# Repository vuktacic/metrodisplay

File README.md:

# MD
## Description
MD (metrodisplay) is a big LED matrix assembly with game controls to play pong and tetris (in progress). It's built with four outdoor (very bright) P5 64x32 panels, a custom pcb with an esp32, a cnc'd wooden frame, and power distribution from mains AC. The total cost of the project is under $90 USD.

I was originally making a small project with a single LED panel to display subway times for the Vancouver Skytrain (hence the name), but I realized that while that was great for a static bedroom display, something much more exciting and interactive like this would be much more fun to showcase at Opensauce!

## TODO List
- [x] Pong game
- [ ] Tetris game (in progress)
- [ ] Concept art
- [ ] CNC designs
- [ ] CNC toolpathing
- [ ] CNCing
- [ ] Frame building
- [ ] Electronics Setup
- [ ] Final tests
- [ ] Dismantling
- [ ] Present at Opensauce!

## Structure
- [./cad](./cad): STEP & F3D
- [./pcb](./pcb): PCB Files.
- [./mdcore](./mdcore): Firmware
- [./bom.csv](./bom.csv): Bill of Materials
- [./JOURNAL.md](./JOURNAL.md): Journal

View the PCB on KiCanvas:  

## CAD
### Frame

Frame designed to be disassembled to fit in standard carry-on luggage.

### Controllers

Controllers are 22cm wide

## Electronics
### PCB

### Schematic

### Power Distribution

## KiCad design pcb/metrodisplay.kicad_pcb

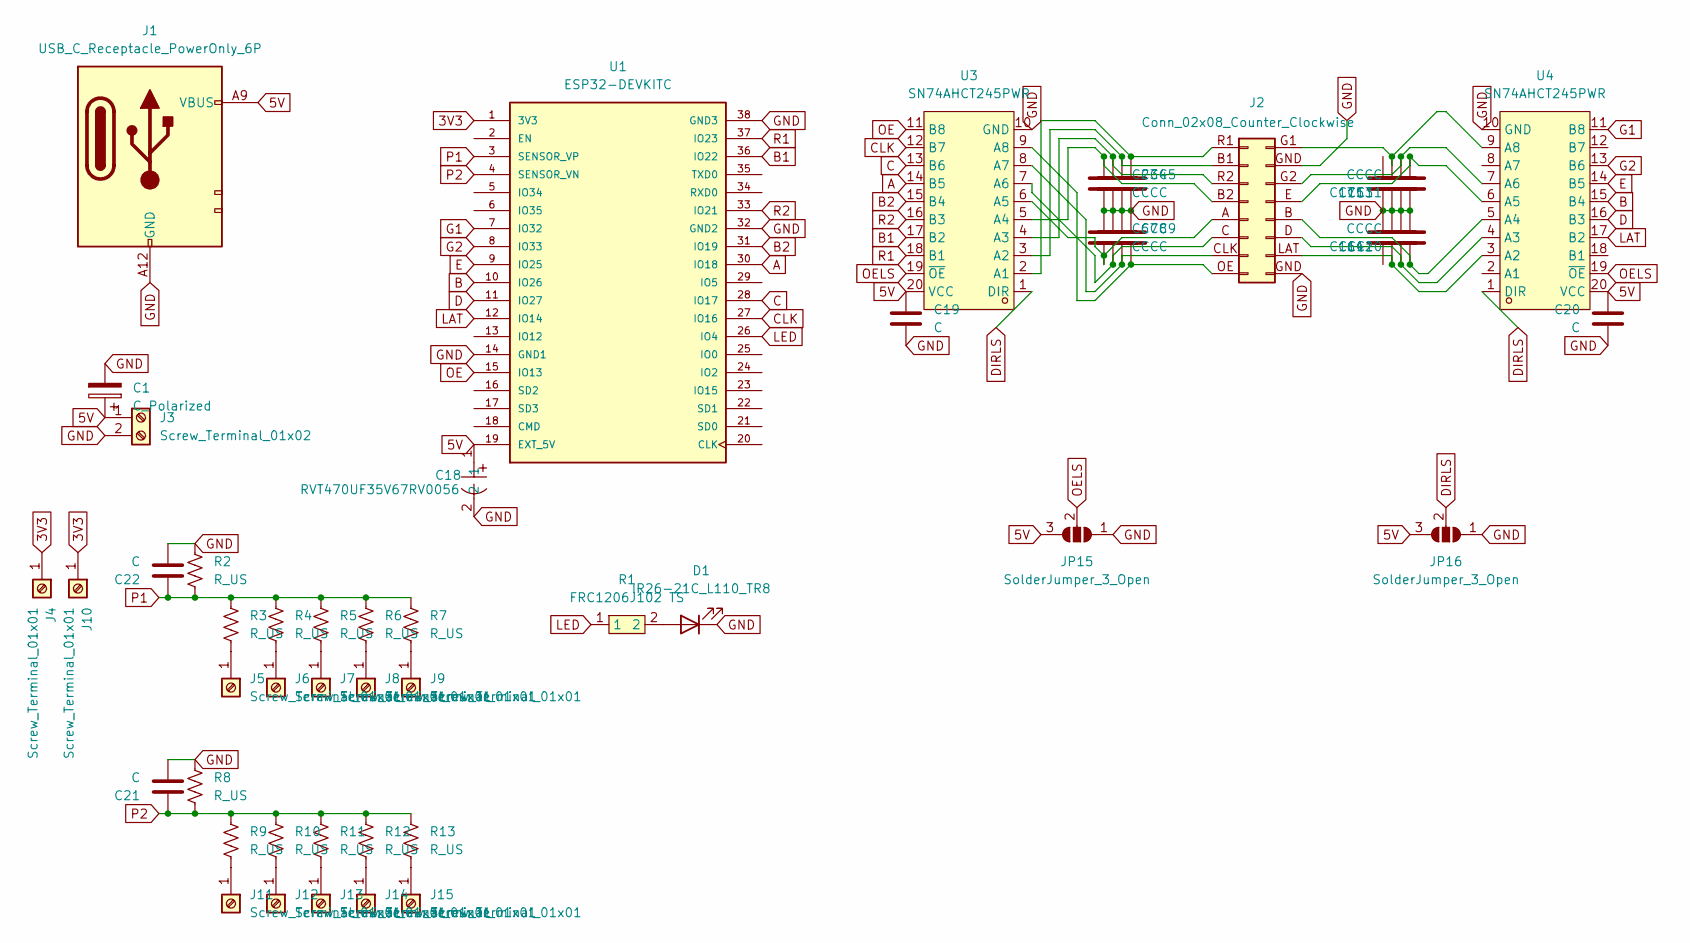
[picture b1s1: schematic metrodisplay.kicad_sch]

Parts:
C1: C_Polarized; CP_Radial_D16.0mm_P7.50mm
C2, C3, C4, C5, C6, C7, C8, C9, C10, C11, C12, C13, C14, C15, C16, C17, C19, C20, C21, C22: C; C1206
C18: RVT470UF35V67RV0056; CAP-SMD_BD10.0-L10.3-W10.3-LS11.0-FD; LCSC Part C2836436
D1: IR26-21C_L110_TR8; LED_1206_3216Metric
J1: USB_C_Receptacle_PowerOnly_6P; USB_C_PD_BOARD
J2: Conn_02x08_Counter_Clockwise; PinHeader_2x08_P2.54mm_Vertical_MD
J3: Screw_Terminal_01x02; TerminalBlock_Dinkle_DT-55-B01X-02_P10.00mm
J4, J5, J6, J7, J8, J9, J10, J11, J12, J13, J14, J15: Screw_Terminal_01x01; SolderWire-0.5sqmm_1x01_D0.9mm_OD2.1mm
JP15, JP16: SolderJumper_3_Open; SolderJumper-3_P2.0mm_Open_TrianglePad1.0x1.5mm
R1: FRC1206J102 TS; R1206; LCSC Part C2907440
R2, R3, R4, R5, R6, R7, R8, R9, R10, R11, R12, R13: R_US; R_Axial_DIN0204_L3.6mm_D1.6mm_P5.08mm_Horizontal
U1: ESP32-DEVKITC; MODULE_ESP32-DEVKITC; PARTREV N/A
U3, U4: SN74AHCT245PWR; TSSOP-20_L6.5-W4.4-P0.65-LS6.4-BL; MPN SN74AHCT245PWR; LCSC Part C10910

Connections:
3V3: J4.1 (Pin_1_1), J10.1 (Pin_1_1), U1.1 (3V3)
5V: C1.1, C18.1, C19.1, C20.1, J1.A9 (VBUS), J3.1, JP15.3 (B), JP16.3 (B), U1.19 (EXT_5V), U3.20 (VCC), U4.20 (VCC)
A: U1.30 (IO18), U3.14 (B5)
B: U1.10 (IO26), U4.15 (B4)
B1: U1.36 (IO22), U3.17 (B2)
B2: U1.31 (IO19), U3.15 (B4)
C: U1.28 (IO17), U3.13 (B6)
CLK: U1.27 (IO16), U3.12 (B7)
D: U1.11 (IO27), U4.16 (B3)
DIRLS: JP16.2 (C), U3.1 (DIR), U4.1 (DIR)
E: U1.9 (IO25), U4.14 (B5)
G1: U1.7 (IO32), U4.11 (B8)
G2: U1.8 (IO33), U4.13 (B6)
GND: C1.2, C2.2, C3.2, C4.2, C5.2, C6.1, C7.1, C8.1, C9.1, C10.2, C11.1, C12.2, C13.1, C14.2, C15.1, C16.2, C17.1, C18.2, C19.2, C20.2, C21.2, C22.2, D1.1 (K), J1.A12 (GND), J2.GND (Pin_9), J3.2, JP15.1 (A), JP16.1 (A), R2.1, R8.1, U1.14 (GND1), U1.32 (GND2), U1.38 (GND3), U3.10 (GND), U4.10 (GND); also elsewhere on the board
LAT: U1.12 (IO14), U4.17 (B2)
LED: R1.1, U1.26 (IO4)
unnamed: D1.2 (A), R1.2
unnamed: C5.1, J2.R1 (Pin_1), U3.2 (A1)
unnamed: C4.1, J2.B1 (Pin_2), U3.3 (A2)
unnamed: C3.1, J2.R2 (Pin_3), U3.4 (A3)
unnamed: C2.1, J2.B2 (Pin_4), U3.5 (A4)
unnamed: C6.2, J2.A (Pin_5), U3.6 (A5)
unnamed: C7.2, J2.C (Pin_6), U3.7 (A6)
unnamed: C8.2, J2.CLK (Pin_7), U3.8 (A7)
unnamed: C9.2, J2.OE (Pin_8), U3.9 (A8)
unnamed: C14.1, J2.LAT (Pin_10), U4.3 (A2)
unnamed: C12.1, J2.D (Pin_11), U4.4 (A3)
unnamed: C10.1, J2.B (Pin_12), U4.5 (A4)
unnamed: C11.2, J2.E (Pin_13), U4.6 (A5)
unnamed: C13.2, J2.G2 (Pin_14), U4.7 (A6)
unnamed: C15.2, J2.G1 (Pin_16), U4.9 (A8)
unnamed 31: J5.1, R3.2; also elsewhere on the board
unnamed: J6.1 (Pin_1_1), R4.2
unnamed: J7.1 (Pin_1_1), R5.2
unnamed: J8.1 (Pin_1_1), R6.2
unnamed: J9.1 (Pin_1_1), R7.2
unnamed: J11.1 (Pin_1_1), R9.2
unnamed: J12.1 (Pin_1_1), R10.2
unnamed: J13.1 (Pin_1_1), R11.2
unnamed: J14.1 (Pin_1_1), R12.2
unnamed: J15.1 (Pin_1_1), R13.2
OE: U1.15 (IO13), U3.11 (B8)
OELS: JP15.2 (C), U3.19 (~OE), U4.19 (~OE)
P1: C22.1, R2.2, R3.1, R4.1, R5.1, R6.1, R7.1, U1.3 (SENSOR_VP); also elsewhere on the board
P2: C21.1, R8.2, R9.1, R10.1, R11.1, R12.1, R13.1, U1.4 (SENSOR_VN)
R1: U1.37 (IO23), U3.18 (B1)
R2: U1.33 (IO21), U3.16 (B3)

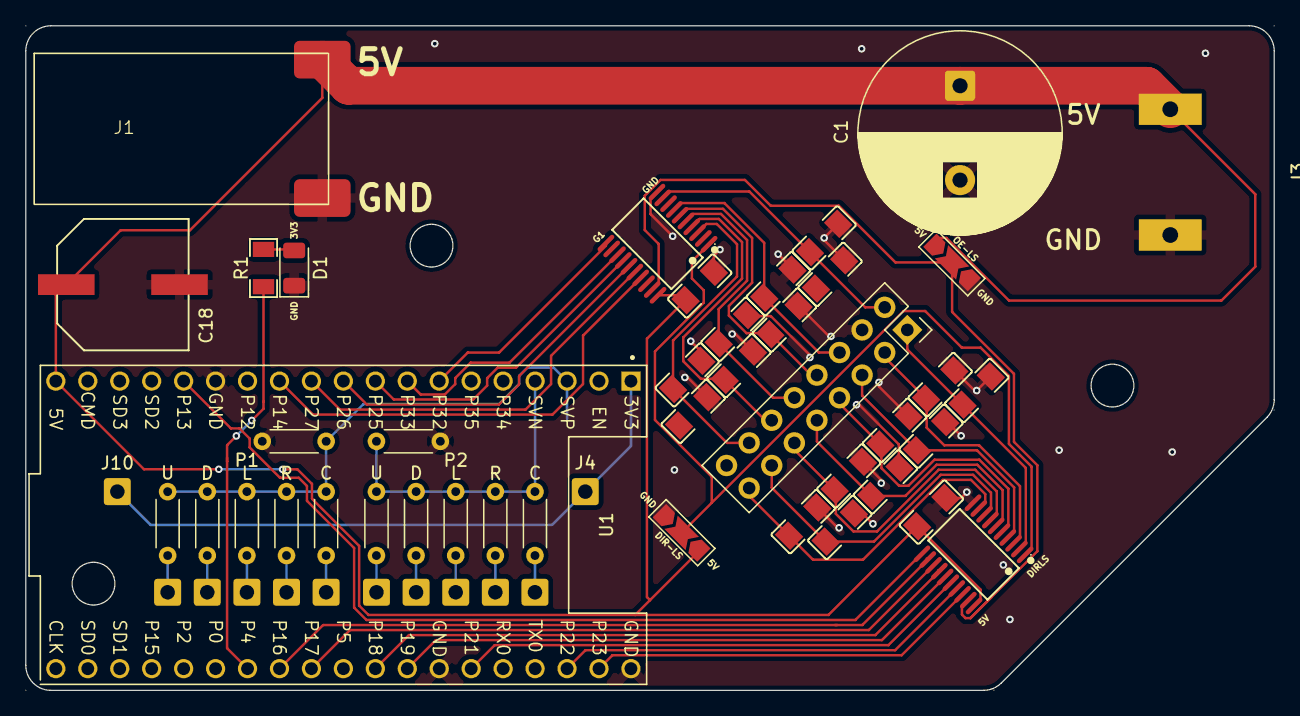
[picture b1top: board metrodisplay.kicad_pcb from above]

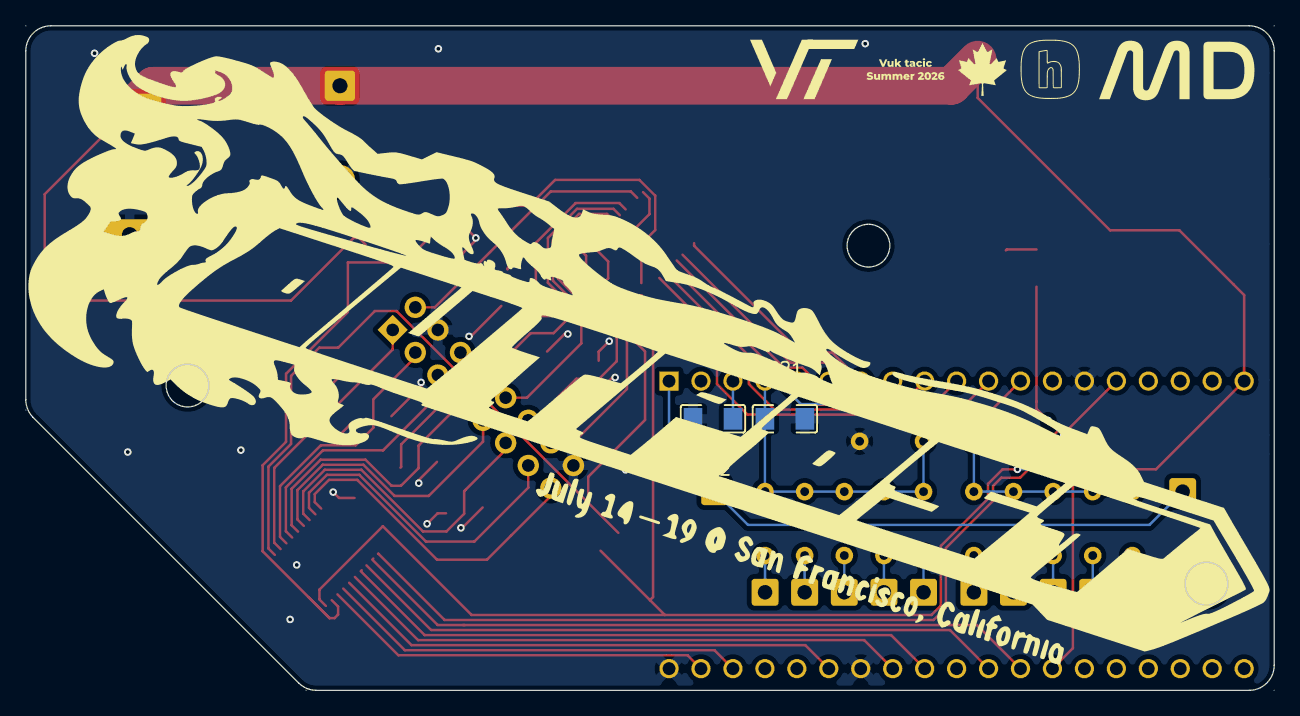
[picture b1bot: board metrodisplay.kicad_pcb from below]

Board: 2 copper layers, 99.2 x 52.8 mm, 56 parts (2 on the bottom side), 47 nets.

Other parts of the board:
P1: R_US; R_Axial_DIN0204_L3.6mm_D1.6mm_P5.08mm_Horizontal
U: Screw_Terminal_01x01; SolderWire-0.5sqmm_1x01_D0.9mm_OD2.1mm

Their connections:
GND: P1.1; also elsewhere on the board
unnamed 31: U.1 (Pin_1_1); also elsewhere on the board
P1: P1.2; also elsewhere on the board

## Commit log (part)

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2026-06-05 Add JOURNAL.md
2026-06-06 Add PCB
2026-06-06 Add LICENSE
2026-06-06 PCB Routing test
2026-06-07 PCB routing done
2026-06-08 PCB done
2026-06-08 Track ./assets/ with git LFS
2026-06-08 Remove artifact
2026-06-10 Enclosure cadded
2026-06-11 Pong game!
2026-06-11 Abstract pong game
2026-06-11 Tetris base
2026-06-11 Base functions
2026-06-11 Journal
2026-06-11 Add updated fusion files
2026-06-11 Update sheets
2026-06-11 BOM & journal
2026-06-11 Fix bom.csv
2026-06-11 Fix bom.csv pt2
2026-06-11 Fix bom.csv pt3
2026-06-11 Add price to README.md
2026-06-11 Add kicanvas to README.md
2026-06-11 Fix kicanvas link
2026-06-12 Add TODO list
2026-06-12 Tetris scaffold
2026-06-12 Pieceshapes
2026-06-12 Move validation
2026-06-12 Clearrows & placing
2026-06-12 Gameover screen
2026-06-12 Add PCB to bom.csv
2026-06-12 Panels
2026-06-16 Journal for June 15th
